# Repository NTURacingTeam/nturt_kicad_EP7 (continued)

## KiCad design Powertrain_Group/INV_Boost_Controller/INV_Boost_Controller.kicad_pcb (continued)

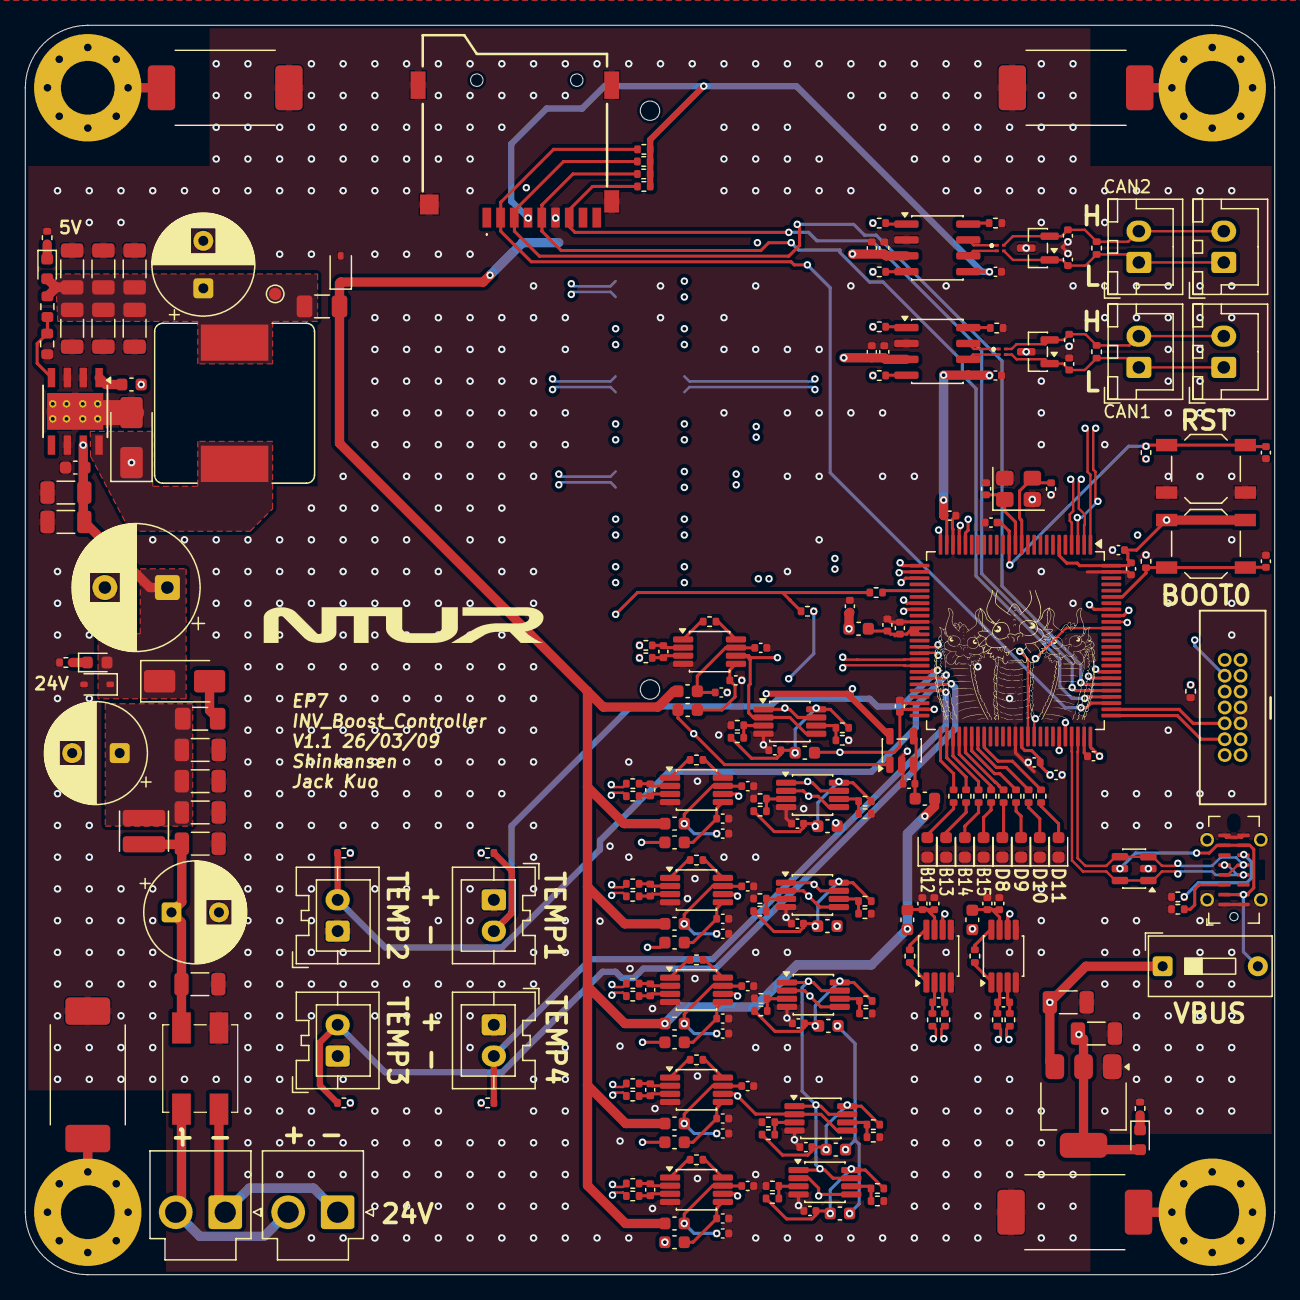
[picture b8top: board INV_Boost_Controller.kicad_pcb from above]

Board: 4 copper layers, 100.0 x 100.0 mm, 261 parts (1 on the bottom side), 183 nets.

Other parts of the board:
C11, C15, C19, C23, C79, C83: 300p; C_0402_1005Metric
R58, R61, R68, R71, R72, R75, R76, R79, R80, R83: 3k43; R_0402_1005Metric
R59, R60, R69, R70, R73, R74, R77, R78, R81, R82: 10k; R_0402_1005Metric

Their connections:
/Diff To Single 1/OCPnode/filt3V3: R80.1, R82.1; also elsewhere on the board
/Diff To Single 3/OCPnode/filt3V3: R58.1, R60.1; also elsewhere on the board
/Diff To Single 4/OCPnode/filt3V3: R68.1, R70.1; also elsewhere on the board
/Diff To Single 5/OCPnode/filt3V3: R72.1, R74.1; also elsewhere on the board
/Diff To Single 6/OCPnode/filt3V3: R76.1, R78.1; also elsewhere on the board
GND: R59.2, R61.2, R69.2, R71.2, R73.2, R75.2, R77.2, R79.2, R81.2, R83.2; also elsewhere on the board
unnamed 143: C11.2; also elsewhere on the board
unnamed 144: C11.1; also elsewhere on the board
unnamed 146: C15.2; also elsewhere on the board
unnamed 147: C15.1; also elsewhere on the board
unnamed 149: C19.2; also elsewhere on the board
unnamed 150: C19.1; also elsewhere on the board
unnamed 152: C23.2; also elsewhere on the board
unnamed 153: C23.1; also elsewhere on the board
unnamed 168: R58.2, R59.1; also elsewhere on the board
unnamed 169: R60.2, R61.1; also elsewhere on the board
unnamed 170: C79.2; also elsewhere on the board
unnamed 171: C79.1; also elsewhere on the board
unnamed 173: C83.2; also elsewhere on the board
unnamed 174: C83.1; also elsewhere on the board
unnamed 175: R68.2, R69.1; also elsewhere on the board
unnamed 176: R70.2, R71.1; also elsewhere on the board
unnamed 177: R72.2, R73.1; also elsewhere on the board
unnamed 178: R74.2, R75.1; also elsewhere on the board
unnamed 179: R76.2, R77.1; also elsewhere on the board
unnamed 180: R78.2, R79.1; also elsewhere on the board
unnamed 181: R80.2, R81.1; also elsewhere on the board
unnamed 182: R82.2, R83.1; also elsewhere on the board
